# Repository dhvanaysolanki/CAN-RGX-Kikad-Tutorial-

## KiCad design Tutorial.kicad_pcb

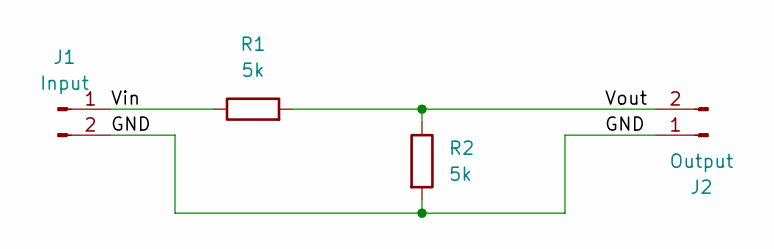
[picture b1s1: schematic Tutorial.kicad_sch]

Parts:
J1: Input; Banana_Jack_2Pin
J2: Output; Banana_Jack_2Pin
R1, R2: 5k; R_1206_3216Metric_Pad1.30x1.75mm_HandSolder

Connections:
/GND: J1.2, J2.1, R2.2
/Vin: J1.1, R1.1
/Vout: J2.2, R1.2, R2.1

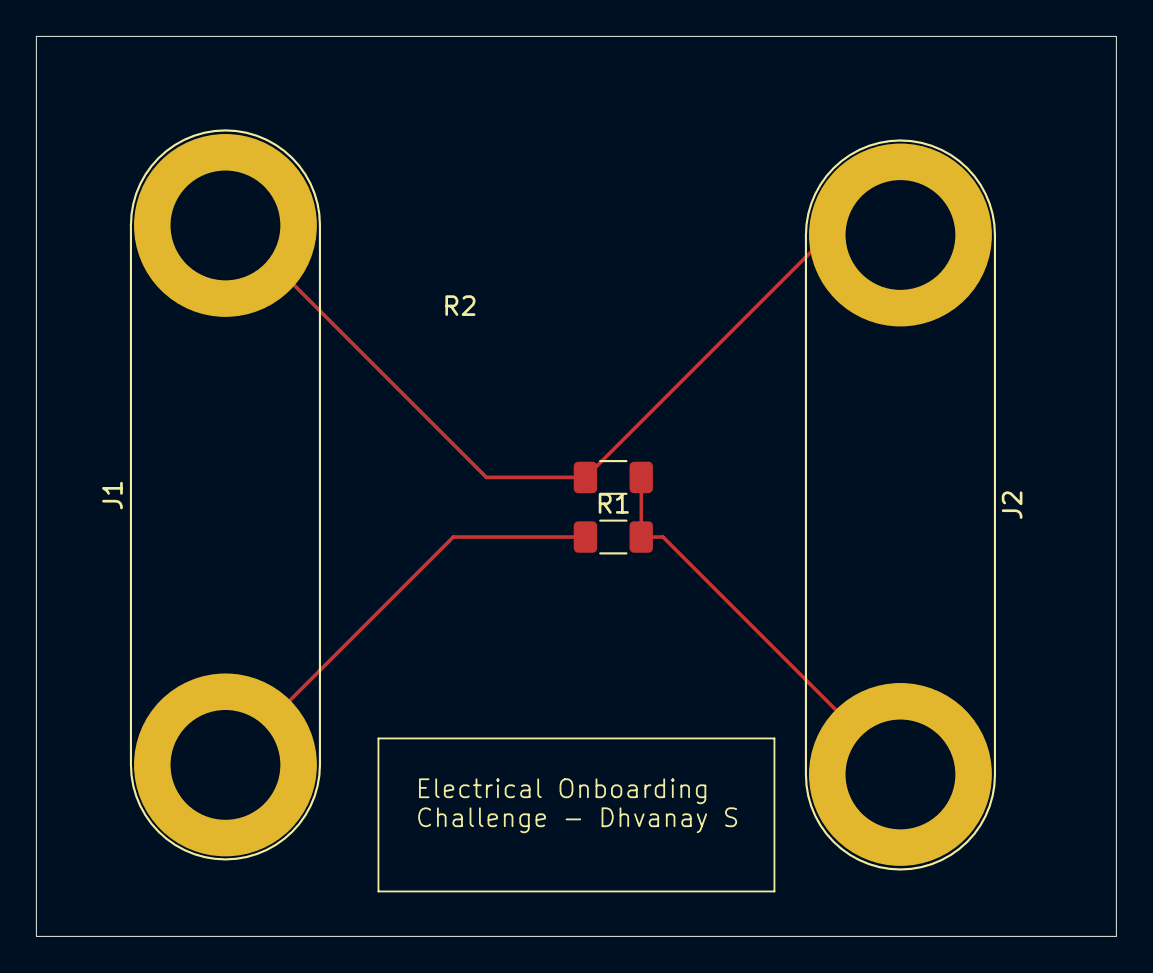
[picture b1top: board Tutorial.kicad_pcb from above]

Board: 2 copper layers, 60.0 x 50.0 mm, 4 parts (0 on the bottom side), 3 nets.
